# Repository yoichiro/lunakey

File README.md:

# Lunakey Project

This project has some keyboards designed by Yoichiro Tanaka.

## Lunakey Mini

Lunakey Mini is a 40% keyboard which has 44 keys and is splitted to left and right. Each side has 3 rows x 6 columns and 4 keys that are pressed by a thumb. Also, it has an ability to light up by Underglow LEDs on the bottom, an ability to display information by OLED modules and an ability to play a sound by a speaker module. Of course, the column-staggered key layout is the result of deep thinking to fit each finger and each key naturally. Lunakey Mini can assist your PC life everyday.

* [Lunakey Mini - Remap](https://remap-keys.app/catalog/BnvcH8rfVvhoT34bsP4r)
* [Build Guide (Japanese only)](https://www.eisbahn.jp/yoichiro/2020/12/lunakey_mini_build_guide_rev4.html)

### Features of Lunakey Mini

* 40% keyboard (3 rows and 6 columns for each side).
* Column-staggered key layout to fit each length of fingers.
* 4 keys for thumb fitted to ranges of movement of the finger naturally.
* Supported both Cherry MX compatible key switches and Kailh Choc low profile key switches.
* Can exchange key switches without soldering by adopting the key sockets.
* Underglow LEDs lighting effect.
* Provides a sound feedback by a piezoelectric speaker.
* OLEDs can put on each side (optional).
* Can customize with [Remap](https://remap-keys.app)

### Necessary Parts

* PCB x 2
* Top plate x 2
* Bottom plate x 2
* Cover plate x 2
* ProMicro x 2
* Head pins (12 pins) x 4
* TRRS socket x 2
* Tact switch (2 feet) x 2
* Diode (1N4148W) x 44
* LED (WS2812B) x 12
* Key socket (Cherry MX Compatible) x 44
* Key socket (Kailh Choc V1) x 44
* piezoelectric speaker (PKLCS1212E4001-R1) x 1
* Register 1kΩ x 1
* M2 spacer 7.5mm x 10
* M2 spacer 10mm x 4
* M2 bolt 5mm x 24
* M2 bolt 3mm x 2
* TRS Cable or TRRS cable x 1
* USB Micro B cable x 1
* Key switch（Cherry MX compatible or Kailh Choc V1） x 44
* Key cap（Cherry MX compatible or Kailh Choc V1, 1U） x 44
* OLED module （with pin socket） x 2 (optional)

## Lunakey Pico

Lunakey Pico is a 40% keyboard which has 44 keys and is splitted to left and right. Each side has 3 rows x 6 columns and 4 keys that are pressed by a thumb. Also, it has an ability to light up by Underglow LEDs on the bottom and an ability to play a sound by a speaker module. Of course, the column-staggered key layout is the result of deep thinking to fit each finger and each key naturally.

The special feature of this Lunakey Pico is that Raspberry Pi Pico has been adopted. Users can use some firmwares: [KMK Firmware](https://github.com/KMKfw/kmk_firmware) and [PRK Firmware](https://github.com/picoruby/prk_firmware).

### Features of Lunakey Pico

* 40% keyboard (3 rows and 6 columns for each side).
* Column-staggered key layout to fit each length of fingers.
* 4 keys for thumb fitted to ranges of movement of the finger naturally.
* Supported both Cherry MX compatible key switches and Kailh Choc low profile key switches.
* Can exchange key switches without soldering by adopting the key sockets.
* Underglow LEDs lighting effect.
* Provides a sound feedback by a piezoelectric speaker.

### Necessary Parts

* PCB x 2
* Top plate x 2
* Bottom plate x 2
* Cover plate x 2
* Raspberry Pi Pico x 2
* Head pins (20 pins) x 4
* TRRS socket x 2
* Tact switch (2 feet) x 2
* Diode (1N4148W) x 44
* LED (WS2812B) x 12
* Key socket (Cherry MX Compatible) x 44
* Key socket (Kailh Choc V1) x 44
* piezoelectric speaker (PKLCS1212E4001-R1) x 1
* Register 1kΩ x 1
* M2 spacer 7.5mm x 10
* M2 spacer 10mm x 4
* M2 bolt 5mm x 24
* M2 bolt 3mm x 2
* TRRS cable x 1
* USB Micro B cable x 1
* Key switch（Cherry MX compatible or Kailh Choc V1） x 44
* Key cap（Cherry MX compatible or Kailh Choc V1, 1U） x 44

Note that TRS (three poles) cable does not work.

## Lunakey Macro

This is a keyboard which has 11 keys only. Users can customize all keys by assigning any key code freely and assigning macros with [Remap](https://remap-keys.app).

* [Lunakey Macro - Remap](https://remap-keys.app/catalog/IY0IjAQ6fM1G3DAKQjmm)

### Features of Lunakey Macro

* 11 keys.
* Supported both Cherry MX compatible key switches.
* Can exchange key switches without soldering by adopting the key sockets.
* Underglow LEDs lighting effect.
* Provides a sound feedback by a piezoelectric speaker.

### Necessary Parts

* PCB x 1
* Top plate x 1
* Bottom plate x 1
* Pro Micro x 1
* Head pins (12 pins) x 2
* Tact switch (2 feet) x 1
* Diode (1N4148W) x 11
* LED Tape (five WS2812B) x 1
* Key socket (Cherry MX Compatible) x 11
* piezoelectric speaker (PKLCS1212E4001-R1) x 1
* Register 1kΩ x 1
* M2 spacer 7.5mm x 4
* M2 bolt 5mm x 4
* USB Micro B cable x 1
* Key switch（Cherry MX compatible） x 11
* Key cap（Cherry MX compatible, 1U） x 11

## For Keyboard Developers

All PCB designs were created with KiCAD. And, all plate designs were drawn with Inkscape. 

### Dependencies

To open each KiCAD project normally, ou need to add following dependencies to your KiCAD as configure paths for each PCB file:

* "YOICHIRO_KBD_PATH" - https://github.com/yoichiro/yoichiro-kbd
* "SPEAKER_PATH" - https://www.snapeda.com/parts/PKLCS1212E4001-R1/Murata/view-part/
* "KBD_PATH" - https://github.com/foostan/kbd
* "KEEBIO_PATH" - https://github.com/keebio/Keebio-Parts.pretty

[foostan/kbd](https://github.com/foostan/kbd): Copyright (C) Kosuke Adachi, all rights reserved and published under MIT License.

[keebio/Keebio-Parts.pretty](https://github.com/keebio/Keebio-Parts.pretty): Copyright (C) Keebio, all rights reserved and published under MIT License.

## License

All files are published under [Lunakey License](https://github.com/yoichiro/lunakey/blob/main/LICENSE). This license consists of dual licenses, for commercial use and non-commercial use. Users who want to use files for the commercial purpose need to agree the commercial-use license. Otherwise, users need to agree the Creative Commons Attribution-NonCommercial-ShareAlike 4.0 International license.

Copyright (C) 2021 Yoichiro Tanaka, all rights reserved.

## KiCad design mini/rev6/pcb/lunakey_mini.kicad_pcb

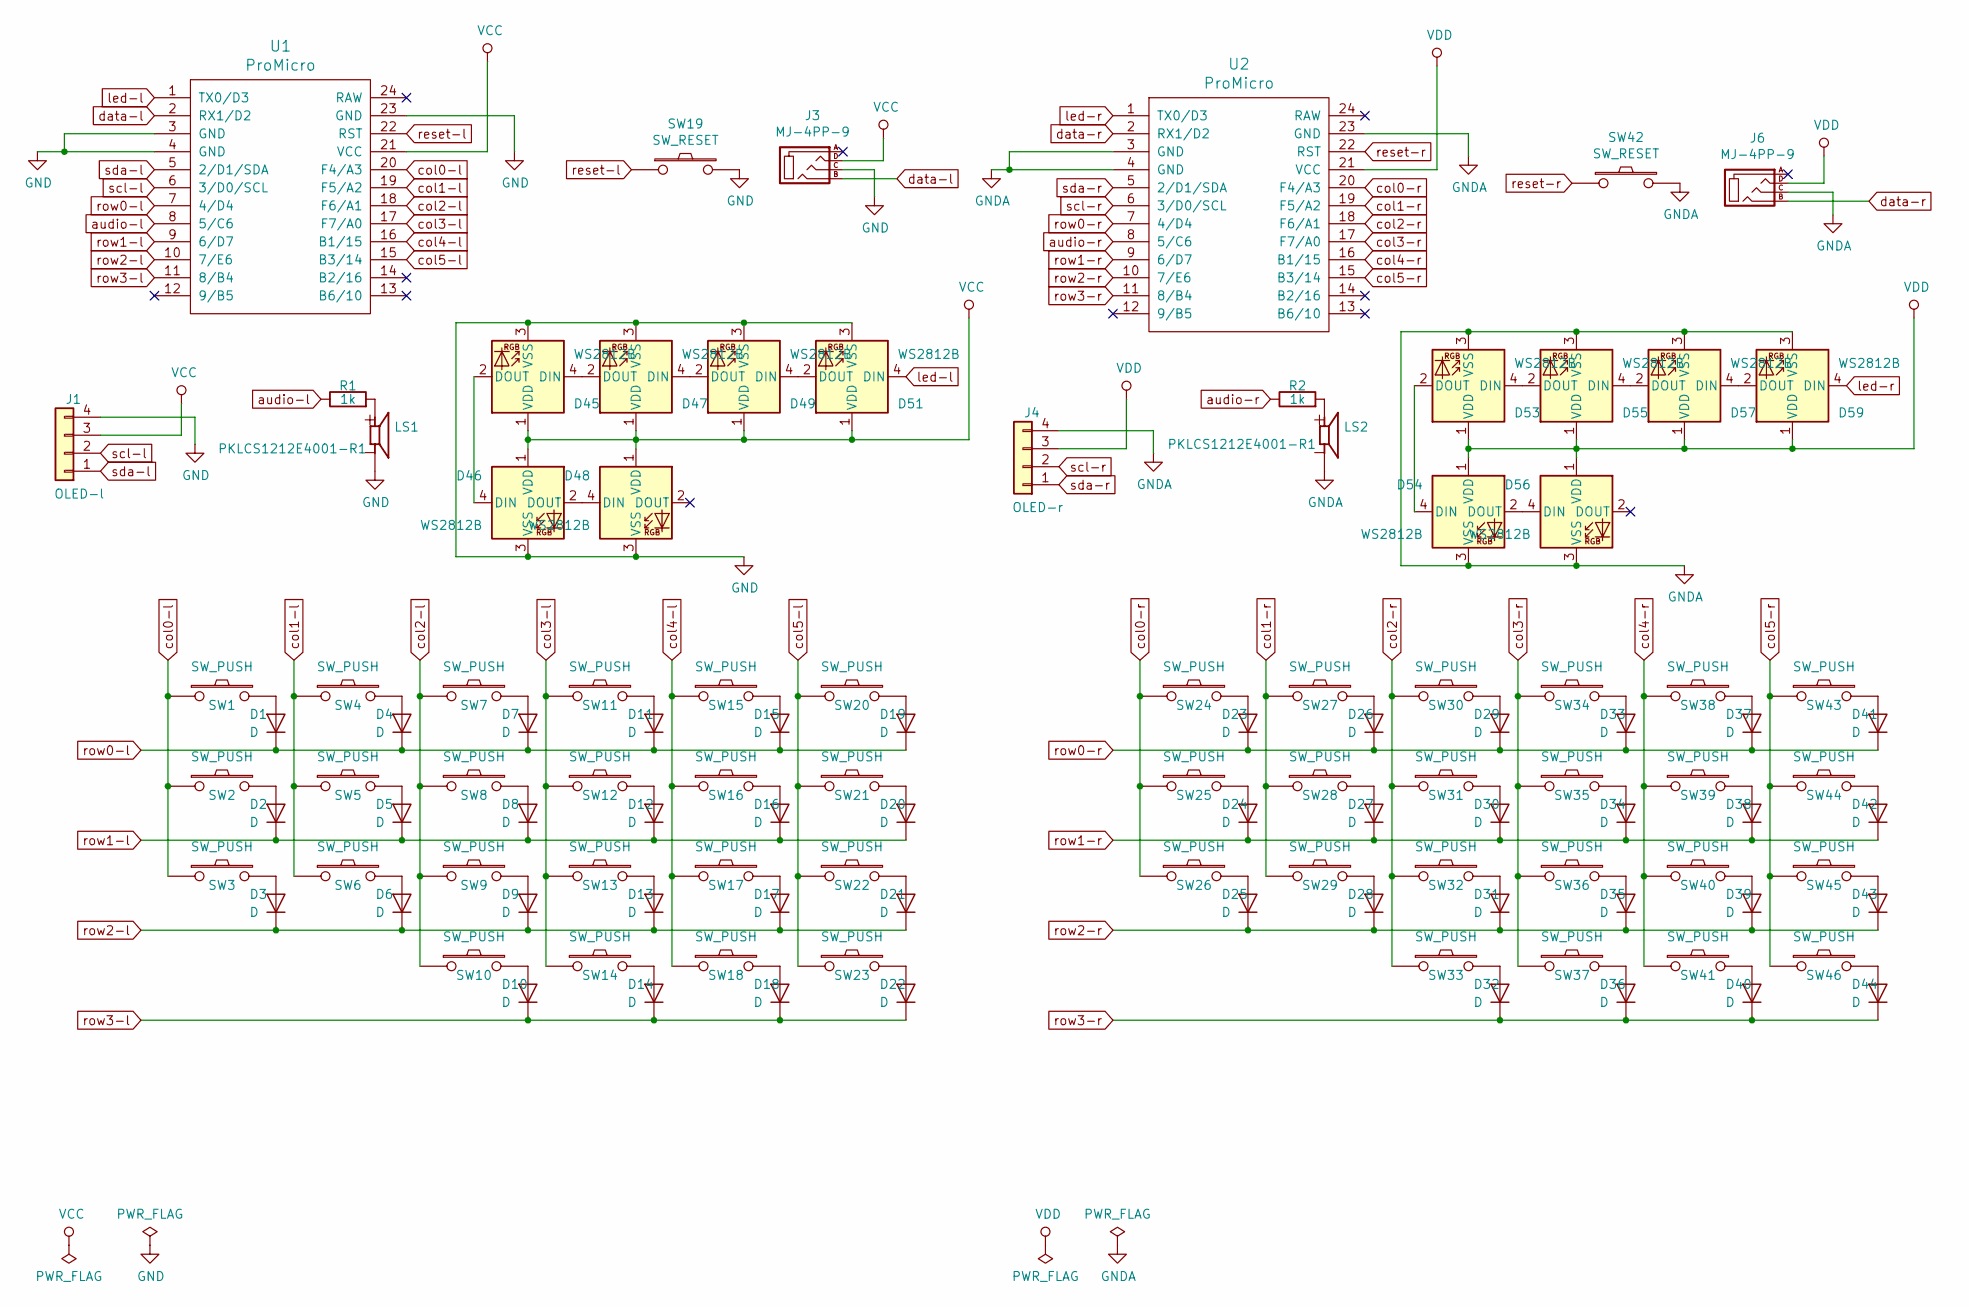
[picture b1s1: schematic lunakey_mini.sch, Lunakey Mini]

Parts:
D1, D2, D3, D4, D5, D6, D7, D8, D9, D10, D11, D12, D13, D14, D15, D16, D17, D18, D19, D20, D21, D22, D23, D24, D25, D26, D27, D28, D29, D30, D31, D32, D33, D34, D35, D36, D37, D38, D39, D40, D41, D42, D43, D44: D; Diode-Hybrid-Back
D45, D46, D47, D48, D49, D51, D53, D54, D55, D56, D57, D59: WS2812B; LED_WS2812B
J1: OLED-l; OLED_v2
J3, J6: MJ-4PP-9; MJ-4PP-9_1side
J4: OLED-r; OLED_v2
LS1, LS2: PKLCS1212E4001-R1; SPKR_PKLCS1212E4001-R1
R1, R2: 1k; Resistor-Hybrid-Back
SW1, SW2, SW3, SW4, SW5, SW6, SW7, SW8, SW9, SW10, SW11, SW12, SW13, SW14, SW15, SW16, SW17, SW18, SW20, SW21, SW22, SW23, SW24, SW25, SW26, SW27, SW28, SW29, SW30, SW31, SW32, SW33, SW34, SW35, SW36, SW37, SW38, SW39, SW40, SW41, SW43, SW44, SW45, SW46: SW_PUSH; CherryMX_Choco_Hotswap
SW19, SW42: SW_RESET; ResetSW_1side
U1, U2: ProMicro; ProMicro_v3

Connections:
GND: D45.3 (VSS), D46.3 (VSS), D47.3 (VSS), D48.3 (VSS), D49.3 (VSS), D51.3 (VSS), J1.4, J3.C, LS1.N, SW19.2, U1.3 (GND), U1.4 (GND), U1.23 (GND)
GNDA: D53.3 (VSS), D54.3 (VSS), D55.3 (VSS), D56.3 (VSS), D57.3 (VSS), D59.3 (VSS), J4.4, J6.C, LS2.N, SW42.2, U2.3 (GND), U2.4 (GND), U2.23 (GND)
unnamed: D1.2 (A), SW1.2
unnamed: D2.2 (A), SW2.2
unnamed: D3.2 (A), SW3.2
unnamed: D4.2 (A), SW4.2
unnamed: D5.2 (A), SW5.2
unnamed: D6.2 (A), SW6.2
unnamed: D7.2 (A), SW7.2
unnamed: D8.2 (A), SW8.2
unnamed: D9.2 (A), SW9.2
unnamed: D10.2 (A), SW10.2
unnamed: D11.2 (A), SW11.2
unnamed: D12.2 (A), SW12.2
unnamed: D13.2 (A), SW13.2
unnamed: D14.2 (A), SW14.2
unnamed: D15.2 (A), SW15.2
unnamed: D16.2 (A), SW16.2
unnamed: D17.2 (A), SW17.2
unnamed: D18.2 (A), SW18.2
unnamed: D19.2 (A), SW20.2
unnamed: D20.2 (A), SW21.2
unnamed: D21.2 (A), SW22.2
unnamed: D22.2 (A), SW23.2
unnamed: D23.2 (A), SW24.2
unnamed: D24.2 (A), SW25.2
unnamed: D25.2 (A), SW26.2
unnamed: D26.2 (A), SW27.2
unnamed: D27.2 (A), SW28.2
unnamed: D28.2 (A), SW29.2
unnamed: D29.2 (A), SW30.2
unnamed: D30.2 (A), SW31.2
unnamed: D31.2 (A), SW32.2
unnamed: D32.2 (A), SW33.2
unnamed: D33.2 (A), SW34.2
unnamed: D34.2 (A), SW35.2
unnamed: D35.2 (A), SW36.2
unnamed: D36.2 (A), SW37.2
unnamed: D37.2 (A), SW38.2
unnamed: D38.2 (A), SW39.2
unnamed: D39.2 (A), SW40.2
unnamed: D40.2 (A), SW41.2
unnamed: D41.2 (A), SW43.2
unnamed: D42.2 (A), SW44.2
unnamed: D43.2 (A), SW45.2
unnamed: D44.2 (A), SW46.2
unnamed: D45.2 (DOUT), D46.4 (DIN)
unnamed: D45.4 (DIN), D47.2 (DOUT)
unnamed: D46.2 (DOUT), D48.4 (DIN)
unnamed: D47.4 (DIN), D49.2 (DOUT)
unnamed: D49.4 (DIN), D51.2 (DOUT)
unnamed: D53.2 (DOUT), D54.4 (DIN)
unnamed: D53.4 (DIN), D55.2 (DOUT)
unnamed: D54.2 (DOUT), D56.4 (DIN)
unnamed: D55.4 (DIN), D57.2 (DOUT)
unnamed: D57.4 (DIN), D59.2 (DOUT)
unnamed: LS1.P, R1.2
unnamed: LS2.P, R2.2
VCC: D45.1 (VDD), D46.1 (VDD), D47.1 (VDD), D48.1 (VDD), D49.1 (VDD), D51.1 (VDD), J1.3, J3.D, U1.21 (VCC)
VDD: D53.1 (VDD), D54.1 (VDD), D55.1 (VDD), D56.1 (VDD), D57.1 (VDD), D59.1 (VDD), J4.3, J6.D, U2.21 (VCC)
audio-l: R1.1, U1.8 (5/C6)
audio-r: R2.1, U2.8 (5/C6)
col0-l: SW1.1, SW2.1, SW3.1, U1.20 (F4/A3)
col0-r: SW24.1, SW25.1, SW26.1, U2.20 (F4/A3)
col1-l: SW4.1, SW5.1, SW6.1, U1.19 (F5/A2)
col1-r: SW27.1, SW28.1, SW29.1, U2.19 (F5/A2)
col2-l: SW7.1, SW8.1, SW9.1, SW10.1, U1.18 (F6/A1)
col2-r: SW30.1, SW31.1, SW32.1, SW33.1, U2.18 (F6/A1)
col3-l: SW11.1, SW12.1, SW13.1, SW14.1, U1.17 (F7/A0)
col3-r: SW34.1, SW35.1, SW36.1, SW37.1, U2.17 (F7/A0)
col4-l: SW15.1, SW16.1, SW17.1, SW18.1, U1.16 (B1/15)
col4-r: SW38.1, SW39.1, SW40.1, SW41.1, U2.16 (B1/15)
col5-l: SW20.1, SW21.1, SW22.1, SW23.1, U1.15 (B3/14)
col5-r: SW43.1, SW44.1, SW45.1, SW46.1, U2.15 (B3/14)
data-l: J3.B, U1.2 (RX1/D2)
data-r: J6.B, U2.2 (RX1/D2)
led-l: D51.4 (DIN), U1.1 (TX0/D3)
led-r: D59.4 (DIN), U2.1 (TX0/D3)
reset-l: SW19.1, U1.22 (RST)
reset-r: SW42.1, U2.22 (RST)
row0-l: D1.1 (K), D4.1 (K), D7.1 (K), D11.1 (K), D15.1 (K), D19.1 (K), U1.7 (4/D4)
row0-r: D23.1 (K), D26.1 (K), D29.1 (K), D33.1 (K), D37.1 (K), D41.1 (K), U2.7 (4/D4)
row1-l: D2.1 (K), D5.1 (K), D8.1 (K), D12.1 (K), D16.1 (K), D20.1 (K), U1.9 (6/D7)
row1-r: D24.1 (K), D27.1 (K), D30.1 (K), D34.1 (K), D38.1 (K), D42.1 (K), U2.9 (6/D7)
row2-l: D3.1 (K), D6.1 (K), D9.1 (K), D13.1 (K), D17.1 (K), D21.1 (K), U1.10 (7/E6)
row2-r: D25.1 (K), D28.1 (K), D31.1 (K), D35.1 (K), D39.1 (K), D43.1 (K), U2.10 (7/E6)
row3-l: D10.1 (K), D14.1 (K), D18.1 (K), D22.1 (K), U1.11 (8/B4)
row3-r: D32.1 (K), D36.1 (K), D40.1 (K), D44.1 (K), U2.11 (8/B4)
scl-l: J1.2, U1.6 (3/D0/SCL)
scl-r: J4.2, U2.6 (3/D0/SCL)
sda-l: J1.1, U1.5 (2/D1/SDA)
sda-r: J4.1, U2.5 (2/D1/SDA)

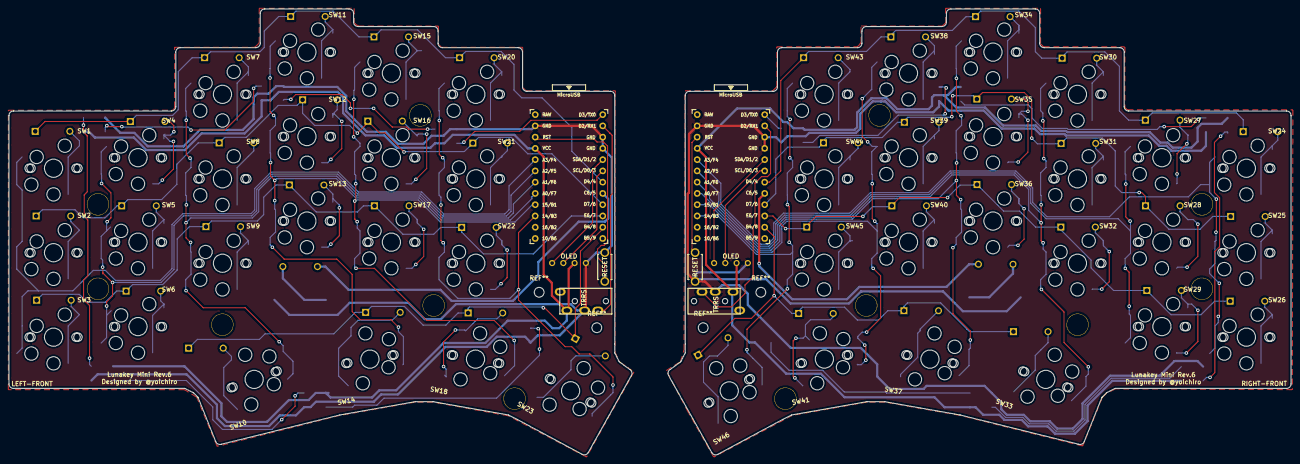
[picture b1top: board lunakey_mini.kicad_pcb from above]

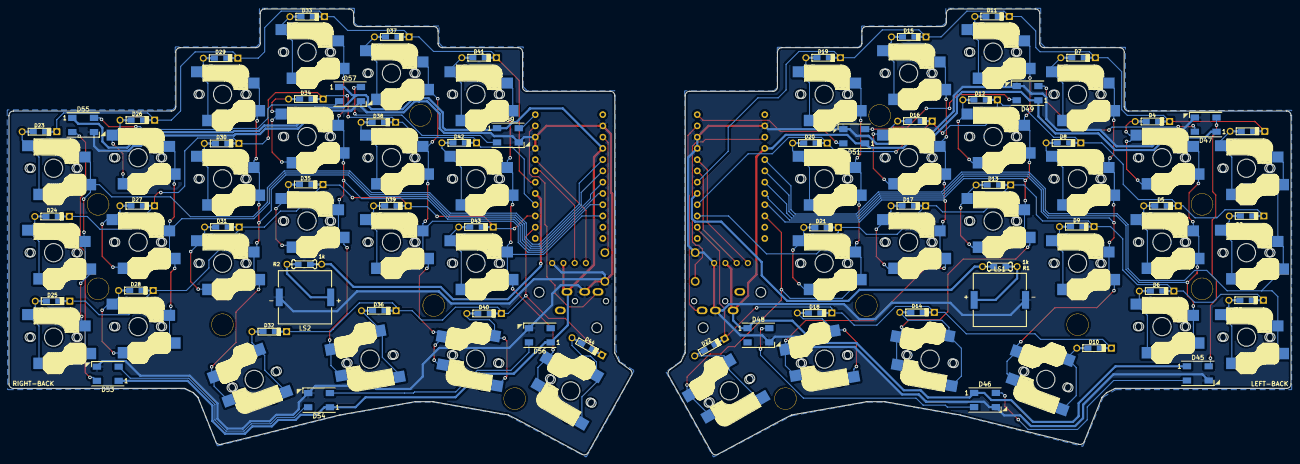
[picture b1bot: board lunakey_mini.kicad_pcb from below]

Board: 2 copper layers, 289.2 x 100.6 mm, 124 parts (14 on the bottom side), 92 nets.

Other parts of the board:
Ref**: Val**; HOLE
Ref**#2, Ref**#3, Ref**#4, Ref**#5, Ref**#6, Ref**#7, Ref**#8, Ref**#9, Ref**#10, Ref**#11, Ref**#12: Val**; HOLE

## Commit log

2021-10-02 Initial commit.
2021-10-03 Update LICENSE
2022-10-03 Lunakey Pico revision 2
